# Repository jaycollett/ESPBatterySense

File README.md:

# ESPBatterySense

This project was inspired by my desire to track the humidity, and to a much lesser degree, the temperature inside the storage solution for my 3D printing filament. To goal was to have a device that is battery operated, lasts several months (if not longer) before needing to recharge or replace batteries, and capable of transmitting to my MQTT broker for display and graphing in HASS.IO. I've been working a lot with ESP-based projects and love the the simplicity of the ESP. In this project, which is a varition of the the original that made use of a BME280 sensor, I've moved to a SI7021-A20 IC that is not a seprate daughter-board which I like better. The SI7021-A20 is a great solution for me as it's easily and affordably sourced, well documented, easy to reflow solder in my homemade solution, and has great accuracy.

The firmware is designed to put the ESP in deep sleep for 1 hour and upon reset, take a sample of humidity, temperature, voltage of battery, and then transmit that to my MQTT broker (which happens to be part of my HASS.IO setup). I originally had been using a LiPo battery from Adafruit, and while it worked, it was providing > 3.6V to the board directly. I never saw any negative issues with such a high voltage from the BME280 sensor or the ESP, but it's not a good design practice and it did cause the ESP to consume far more power in deep sleep than voltages closer to 3.3V. For these reasons, I've switched to (2) AA alkaline batteries and have had great longevity thus far with them. Running the prototype design for well over 3 weeks with a tenth of a volt drop on the batteries.

Unfortunately, this design requires a reflow solution as the SI7021 is not something I would classify as easily hand soldered. 

**BOM**
----------
1. [ESP-12S](https://www.aliexpress.com/item/ESP8266-ESP-12E-serial-WIFI-wireless-module-wireless-transceiver-Complete-circuit-impedance-matching-better-signal/32324777806.html)
2. [SI7021-A20](https://www.aliexpress.com/item/100-brand-new-original-Si7021-A20-GM1R-Si7021-A20/32834030103.html) (with protective cover and A20 version not A10)
3. 10K OHM 0805 Resistor (QTY: 5)
4. 0.1UF Ceramic Capacitor X7R 16V 0805 (QTY: 1)
6. [Custom PCB](https://oshpark.com/shared_projects/1hOMQGI8) from OSHPark.com
7. [JST connector](https://www.digikey.com/product-detail/en/jst-sales-america-inc/S2B-PH-K-S%28LF%29%28SN%29/455-1719-ND/926626) for battery
7. Battery (any ~3.3V battery source, I'm using 2 alkaline AA batteries)
8. Optional header for programming and debug pins
9. Enclosure of some sort (my very basic design is [here](https://www.thingiverse.com/thing:3371715)
#

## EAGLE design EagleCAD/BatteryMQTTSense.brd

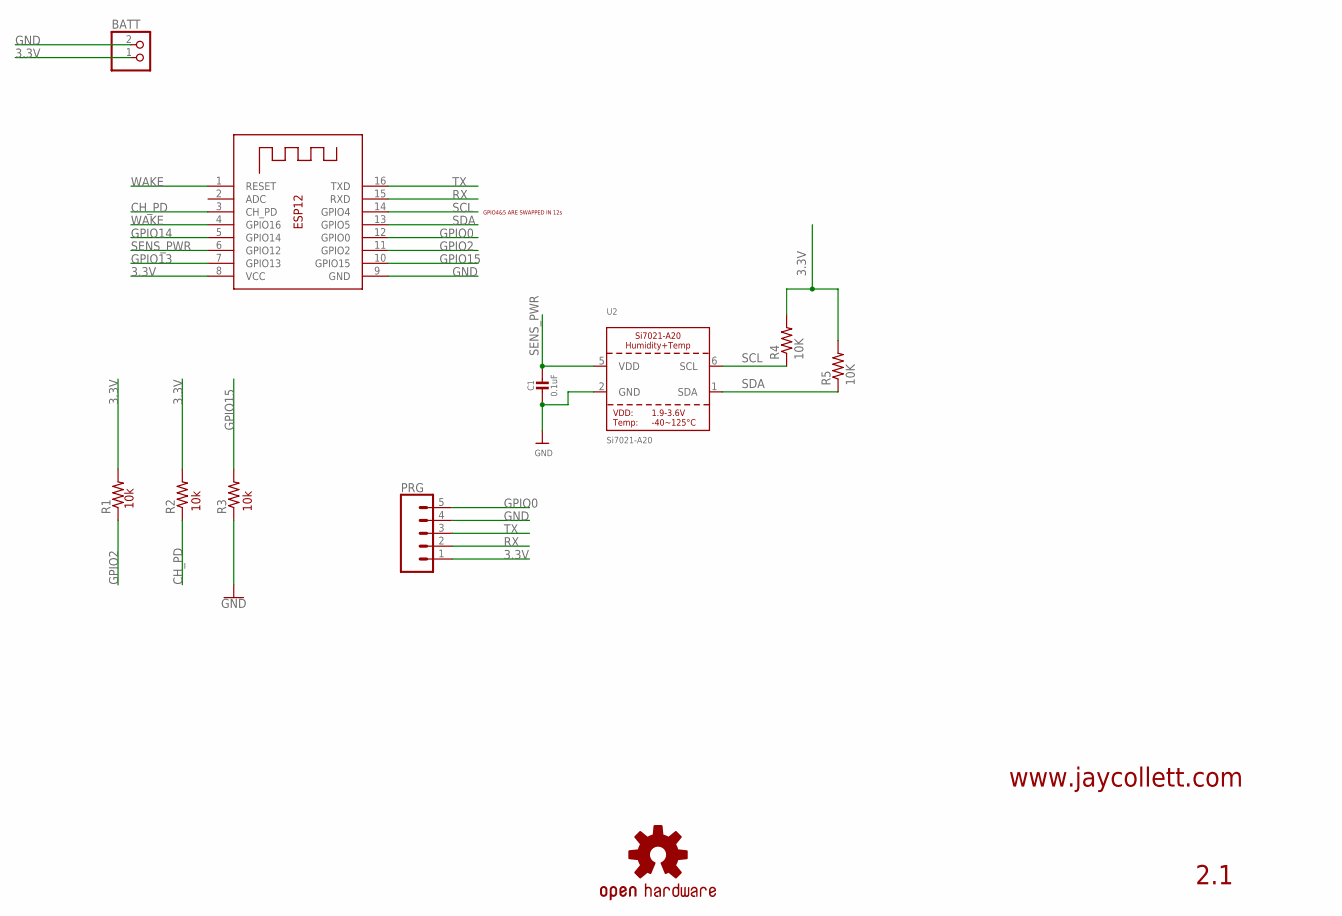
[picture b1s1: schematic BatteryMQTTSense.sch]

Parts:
BATT: JST_2PIN-THM-RA; JST-PH-2-THM-RA
C1: 0.1uF; 0805-NO
LOGO1: OSHW-LOGOS; OSHW-LOGO-S
PRG: CONN_05PTH_LONGPADS; 1X05_LONGPADS
R1, R2, R3: R-US_M0805; M0805
R4, R5: 10K; M0805
U2: Si7021-A20; DFN6_3X3_SI
_: ESP-12

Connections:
3.3V: BATT.1 (2), PRG.1, R1.2, R2.2, R4.2, R5.2, _.8 (VCC)
CH_PD: R2.1, _.3 (CH_PD)
GND: BATT.2 (1), C1.2, PRG.4, R3.1, U2.2 (GND), _.9 (GND)
GPIO0: PRG.5, _.12 (GPIO0)
GPIO2: R1.1, _.11 (GPIO2)
GPIO13: _.7 (GPIO13)
GPIO14: _.5 (GPIO14)
GPIO15: R3.2, _.10 (GPIO15)
RX: PRG.2, _.15 (RXD)
SCL: R4.1, U2.6 (SCL), _.14 (GPIO4)
SDA: R5.1, U2.1 (SDA), _.13 (GPIO5)
SENS_PWR: C1.1, U2.5 (VDD), _.6 (GPIO12)
TX: PRG.3, _.16 (TXD)
WAKE: _.1 (RESET), _.4 (GPIO16)

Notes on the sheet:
www.jaycollett.com
10k
GPIO4&5 ARE SWAPPED IN 12s
2.1

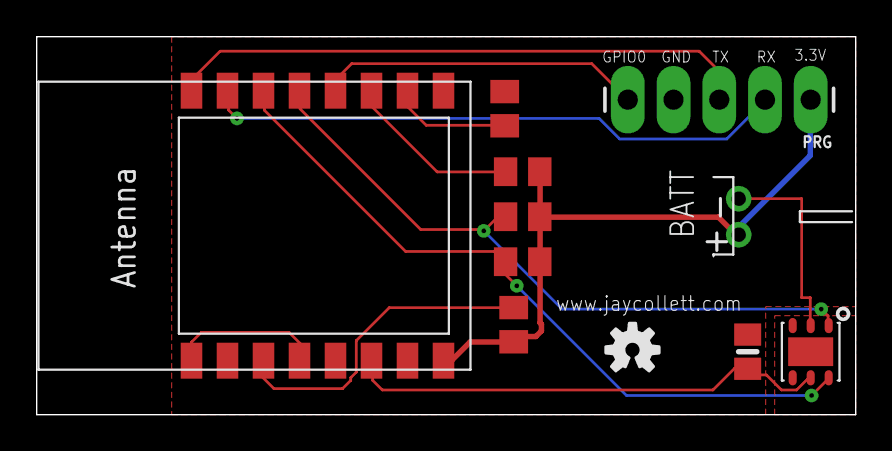
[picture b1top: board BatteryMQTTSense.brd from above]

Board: 2 copper layers, 45.5 x 21.0 mm, 11 parts (0 on the bottom side), 12 nets.

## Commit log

2018-03-21 adding arduino stubs
2018-03-21 arduino sketch stub
2018-03-25 adding version 0.1a firmware
2018-03-25 adding gitignore
2018-03-26 first development version complete v0.1a
2018-03-26 updating Arduino folder structure
2018-03-26 adding travis file
2018-03-26 updating readme with badges
2018-03-27 adding code to power the dht on pin 0
2018-03-31 adding eagle files for board v1.0
2018-04-09 adding new design for eaglecad files, using daughterboard for bme
2018-04-09 updating schematic and board and added png file versions
2018-04-09 updating code to work with 12f and bme280
2018-04-09 updating firmware to fix pin mapping issue
2018-04-26 modifing code to fix issue with deepsleep zombie mode...
2018-04-29 attempting to fix accuracy issues of sensor readings..
2018-05-05 Using Sparkfun library, validated readings
2018-05-05 Update travis file for new SF library
2018-12-13 first version of PCB for SI Sensor version
2018-12-23 update arduino code to support SI7021 sensor and clean up delays
2018-12-23 update travis file for new SI7021 library
2019-01-14 fixing issue with sensor proxmity to mcu and other tweaks
2019-01-15 Update README.md
    updated link to pcb on oshpark
2019-01-21 pushing validated version of board and firmware, including stl files for enclosure
2024-01-20 Updates debug serial out text, tweaks to try to save a bit more power
2024-01-21 Removed debug define, ready for config and burning to 12s chips
2024-10-08 Updates firmware to prevent battery drain on failed Wifi connection.
2024-10-08 updated firmware
2025-01-22 Adds logic to retry wifi.
2025-01-22 Adds logic to dynamically create device CHIPID base topic and includes calculated battery percentage topic
2025-01-22 Adds more refined logic to MQTT to reduce time alive. Adds more error logic
2025-01-22 Removes the capacity, cleans up code.
2025-01-22 Fixes bug with JSON payload having a space before the vcc value. Bumps version number to 3.2
2025-01-23 Adds updated function for sensor reading, consistent with vcc function, other small tweaks.
2026-02-05 Updates firmware for even more battery life savings. Mainly Quick connect to WiFi by caching BSSID, etc. tweaks to sensor timings, etc.

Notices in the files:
parts and their libraries:
SparkFun-Aesthetics: Licensing: Creative Commons ShareAlike 4.0 International - https://creativecommons.org/licenses/by-sa/4.0
microbuilder: This work is placed in the public domain, and may be freely used for commercial and non-commercial work with the following conditions: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
